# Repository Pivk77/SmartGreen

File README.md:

# SmartGreen

Smart watering project for your garden. It uses multiple sensors such as ultrasonic depth measurement of your watering tank, humidity sensors, and online weather forecast.

## Usage/Examples

In this repository you are provided with in-detailed schematics of the PCB-board for diy purposes. In the future you might be able to buy the PCB.

The device is meant to be used with [ESPHOME](https://esphome.io/) installed onto and work in conjunction with [HomeAssistant](https://www.home-assistant.io/).

The device uses 12VDC power input. There are 5 230V/16A relays installed onto it so you can connect devices up to 230V (could be less). I've used them as switches for garden pumps and electromagnetic valves.

It also has the built in connector for [SR04M](https://www.google.com/search?q=sr04m) ultrasonic sensor i've used to detect the level of water in a tank.
## Authors

- [@Pivk77](https://github.com/Pivk77)

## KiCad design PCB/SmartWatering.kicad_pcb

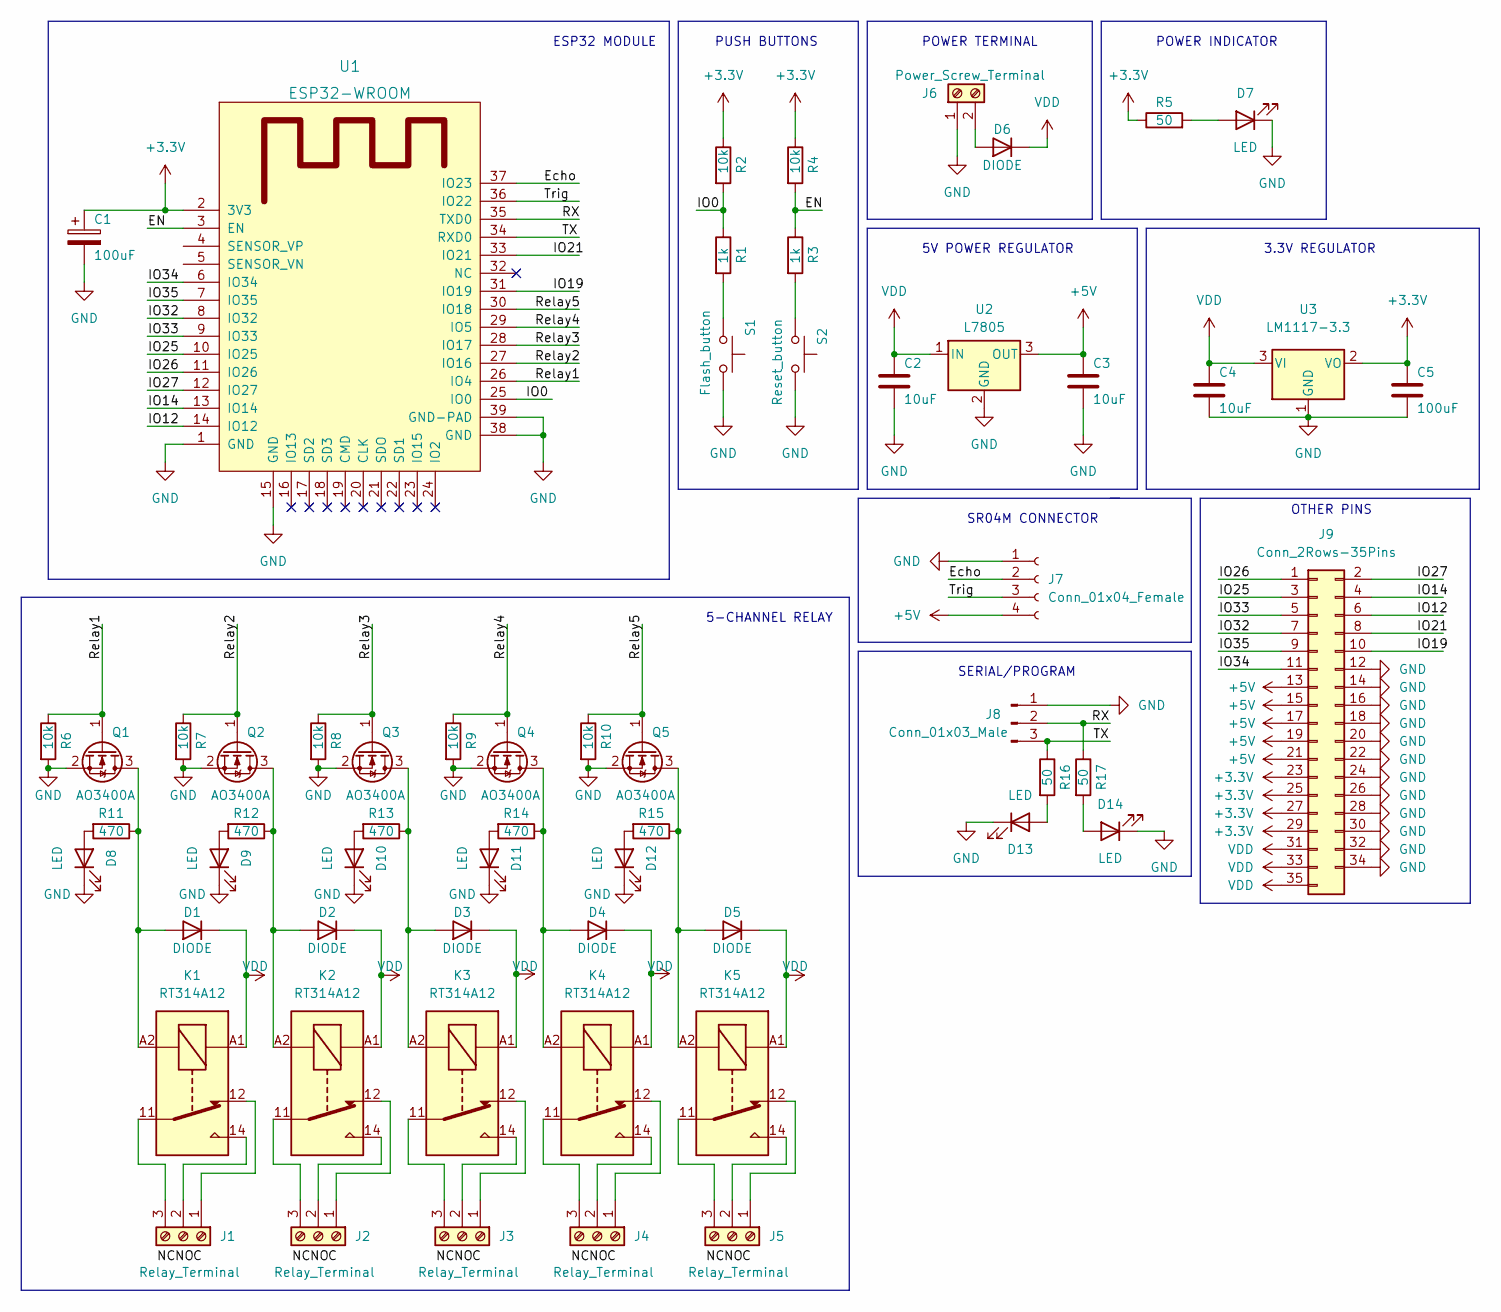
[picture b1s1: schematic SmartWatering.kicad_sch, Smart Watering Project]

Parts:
C1: 100uF; CP_Radial_D6.3mm_P2.50mm
C2, C3, C4: 10uF; C_0805_2012Metric_Pad1.18x1.45mm_HandSolder
C5: 100uF; C_0805_2012Metric_Pad1.18x1.45mm_HandSolder
D1, D2, D3, D4, D5, D6: DIODE; D_SMA_Handsoldering
D7, D8, D9, D10, D11, D12, D13, D14: LED; LED_0805_2012Metric_Pad1.15x1.40mm_HandSolder
J1, J2, J3, J4, J5: Relay_Terminal; TerminalBlock_Phoenix_MPT-0,5-3-2.54_1x03_P2.54mm_Horizontal
J6: Power_Screw_Terminal; TerminalBlock_Phoenix_MPT-0,5-2-2.54_1x02_P2.54mm_Horizontal
J7: Conn_01x04_Female; PinHeader_1x04_P2.54mm_Vertical
J8: Conn_01x03_Male; PinHeader_1x03_P2.54mm_Vertical
J9: Conn_2Rows-35Pins; PinHeader_2x18_P2.54mm_Vertical
K1, K2, K3, K4, K5: RT314A12; Relay_SPDT_Schrack-RT1-16A-FormC_RM5mm
Q1, Q2, Q3, Q4, Q5: AO3400A; SOT-23
R1, R3: 1k; R_0805_2012Metric_Pad1.20x1.40mm_HandSolder
R2, R4, R6, R7, R8, R9, R10: 10k; R_0805_2012Metric_Pad1.20x1.40mm_HandSolder
R5, R16, R17: 50; R_0805_2012Metric_Pad1.20x1.40mm_HandSolder
R11, R12, R13, R14, R15: 470; R_0805_2012Metric_Pad1.20x1.40mm_HandSolder
S1: Flash_button; SW_SPST_SKQG_WithoutStem
S2: Reset_button; SW_SPST_SKQG_WithoutStem
U1: ESP32-WROOM
U2: L7805; SOT-223-3_TabPin2
U3: LM1117-3.3; SOT-223-3_TabPin2

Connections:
+3V3: C1.1, C5.1, J9.23, J9.25, J9.27, J9.29, R2.1, R4.1, R5.1, U1.2 (3V3), U3.2 (VO)
+5V: C3.1, J7.4, J9.13, J9.15, J9.17, J9.19, J9.21, U2.3 (OUT)
/EN: R3.1, R4.2, U1.3 (EN)
/Echo: J7.2, U1.37 (IO23)
/IO0: R1.1, R2.2, U1.25 (IO0)
/IO12: J9.6, U1.14 (IO12)
/IO14: J9.4, U1.13 (IO14)
/IO19: J9.10, U1.31 (IO19)
/IO21: J9.8, U1.33 (IO21)
/IO25: J9.3, U1.10 (IO25)
/IO26: J9.1, U1.11 (IO26)
/IO27: J9.2, U1.12 (IO27)
/IO32: J9.7, U1.8 (IO32)
/IO33: J9.5, U1.9 (IO33)
/IO34: J9.11, U1.6 (IO34)
/IO35: J9.9, U1.7 (IO35)
/RX: J8.2, R17.1, U1.35 (TXD0)
/Relay1: Q1.1 (G), R6.1, U1.26 (IO4)
/Relay2: Q2.1 (G), R7.1, U1.27 (IO16)
/Relay3: Q3.1 (G), R8.1, U1.28 (IO17)
/Relay4: Q4.1 (G), R9.1, U1.29 (IO5)
/Relay5: Q5.1 (G), R10.1, U1.30 (IO18)
/TX: J8.3, R16.1, U1.34 (RXD0)
/Trig: J7.3, U1.36 (IO22)
GND: C1.2, C2.2, C3.2, C4.2, C5.2, D7.1 (K), D8.1 (K), D9.1 (K), D10.1 (K), D11.1 (K), D12.1 (K), D13.1 (K), D14.1 (K), J6.1, J7.1, J8.1, J9.12, J9.14, J9.16, J9.18, J9.20, J9.22, J9.24, J9.26, J9.28, J9.30, J9.32, J9.34, Q1.2 (S), Q2.2 (S), Q3.2 (S), Q4.2 (S), Q5.2 (S), R6.2, R7.2, R8.2, R9.2, R10.2, S1.2, S2.2, U1.1 (GND), U1.15 (GND), U1.38 (GND), U1.39 (GND-PAD), U2.2 (GND), U3.1 (GND)
unnamed: D1.1 (A), K1.A2, Q1.3 (D), R11.1
unnamed: D2.1 (A), K2.A2, Q2.3 (D), R12.1
unnamed: D3.1 (A), K3.A2, Q3.3 (D), R13.1
unnamed: D4.1 (A), K4.A2, Q4.3 (D), R14.1
unnamed: D5.1 (A), K5.A2, Q5.3 (D), R15.1
unnamed: D6.1 (A), J6.2
unnamed: D7.2 (A), R5.2
unnamed: D8.2 (A), R11.2
unnamed: D9.2 (A), R12.2
unnamed: D10.2 (A), R13.2
unnamed: D11.2 (A), R14.2
unnamed: D12.2 (A), R15.2
unnamed: D13.2 (A), R16.2
unnamed: D14.2 (A), R17.2
unnamed: J1.1, K1.12
unnamed: J1.2, K1.14
unnamed: J1.3, K1.11
unnamed: J2.1, K2.12
unnamed: J2.2, K2.14
unnamed: J2.3, K2.11
unnamed: J3.1, K3.12
unnamed: J3.2, K3.14
unnamed: J3.3, K3.11
unnamed: J4.1, K4.12
unnamed: J4.2, K4.14
unnamed: J4.3, K4.11
unnamed: J5.1, K5.12
unnamed: J5.2, K5.14
unnamed: J5.3, K5.11
unnamed: R1.2, S1.1
unnamed: R3.2, S2.1
VDD: C2.1, C4.1, D1.2 (K), D2.2 (K), D3.2 (K), D4.2 (K), D5.2 (K), D6.2 (K), J9.31, J9.33, J9.35, K1.A1, K2.A1, K3.A1, K4.A1, K5.A1, U2.1 (IN), U3.3 (VI)

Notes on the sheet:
5V POWER REGULATOR
POWER TERMINAL
5-CHANNEL RELAY
POWER INDICATOR
SR04M CONNECTOR
3.3V REGULATOR
SERIAL/PROGRAM
PUSH BUTTONS
OTHER PINS
ESP32 MODULE

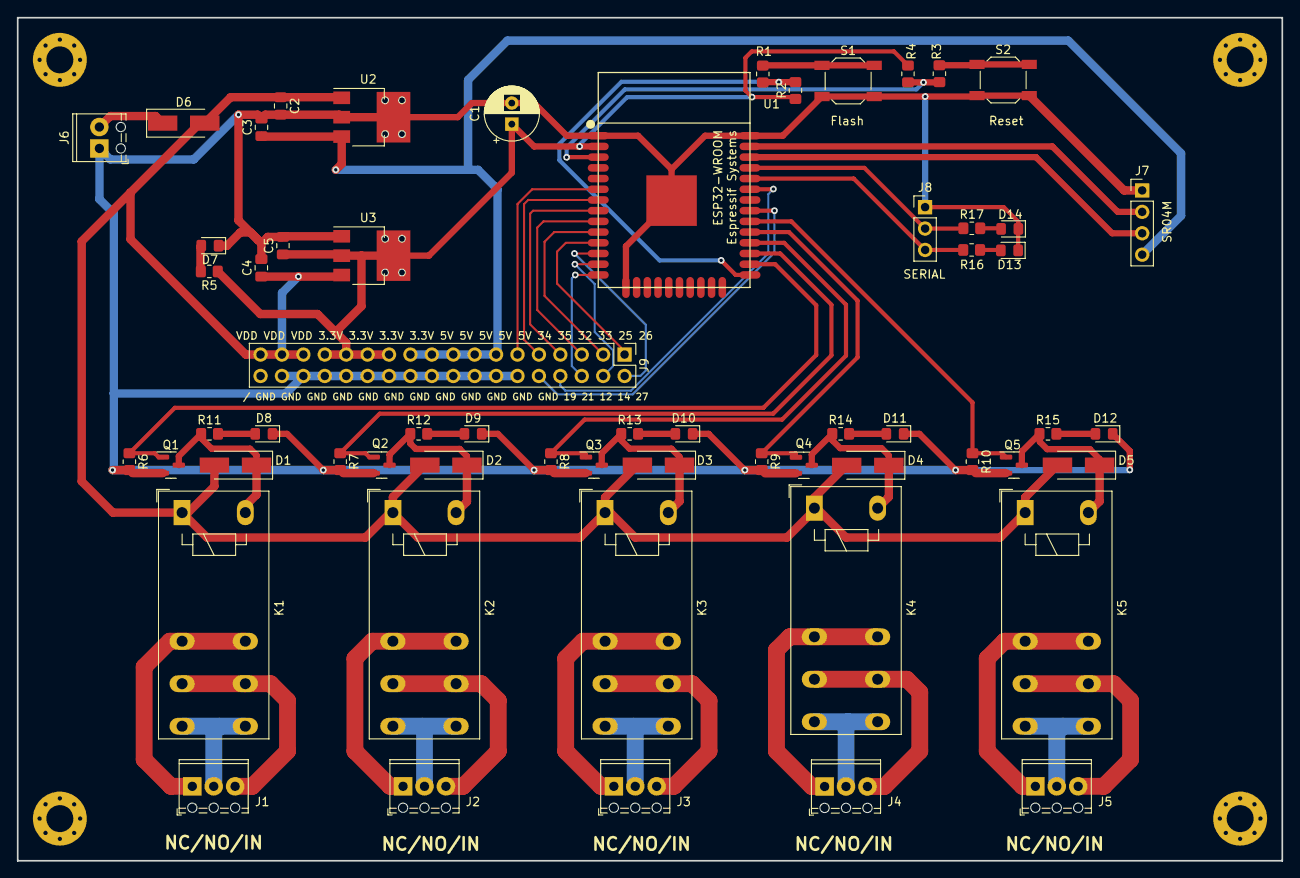
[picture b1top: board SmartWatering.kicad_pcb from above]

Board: 2 copper layers, 150.0 x 100.0 mm, 65 parts (1 on the bottom side), 57 nets.

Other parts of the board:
 : MountingHole_3.2mm_M3_Pad_Via
 #2,  #3,  #4: MountingHole_3.2mm_M3_Pad_Via
 #5: LOGO; smartgreen-logo

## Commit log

2022-05-26 Changed github language display
2022-05-27 Some changes to the wiring, added connector for other pins currently not in use
2022-05-30 Minor changes
2022-06-02 Changed non-used pins on esp external connector
2022-06-14 Bug fixes and ready for production
2022-06-14 Cleanup
